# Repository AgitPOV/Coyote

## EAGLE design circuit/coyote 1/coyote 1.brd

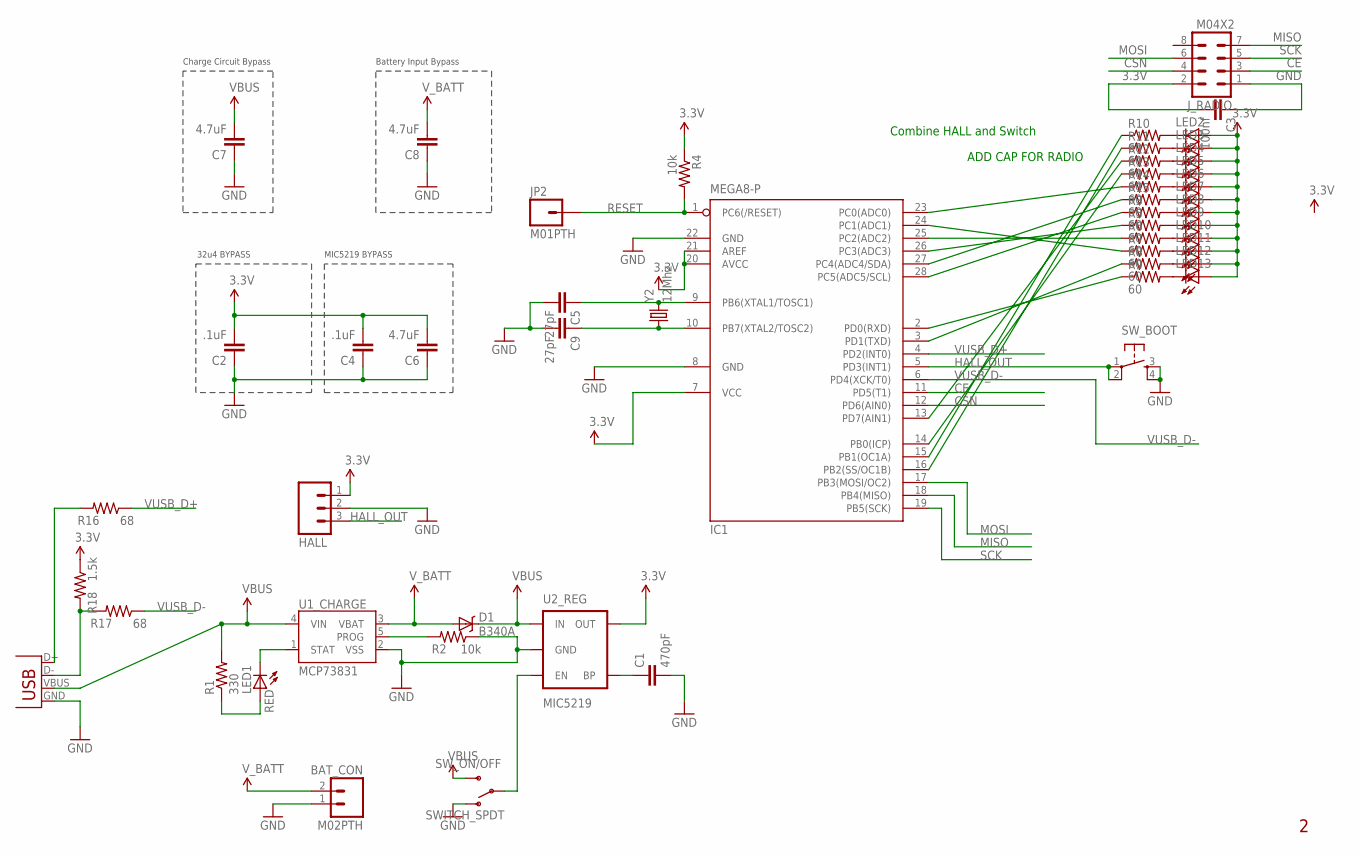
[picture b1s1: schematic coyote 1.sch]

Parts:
BAT_CON: M02PTH; 1X02
C1: 470pF; 1206
C2, C4: .1uF; 1206
C3: 100nf; 1206
C5, C9: 27pF; 1206
C6, C7, C8: 4.7uF; 1206
D1: B340A; SMA-DIODE
HALL: M03PTH; 1X03
IC1: MEGA8-P; DIL28-3
JP1: USB-MB-H
JP2: M01PTH; 1X01
J_RADIO: M04X2; 2X4
LED1: RED; LED-1206
LED2, LED3, LED4, LED5, LED6, LED7, LED8, LED9, LED10, LED11, LED12, LED13: LED1206; LED-1206
R1: 330; 1206
R2, R4: 10k; 1206
R3, R5, R6, R7, R8, R9, R10, R11, R12, R13, R14, R15: 60; 1206
R16, R17: 68; 1206
R18: 1.5k; 1206
SW_BOOT: TAC_SWITCHPTH; TACTILE-PTH
SW_ON/OFF: SWITCH_SPDT; KPS-1290
U1_CHARGE: MCP73831; SOT23-5
U2_REG: MIC5219; SOT23-5
Y2: 12Mhz; HC49US

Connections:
3.3V: C2.2, C3.2, C4.2, C6.2, HALL.1, IC1.7 (VCC), IC1.20 (AVCC), IC1.21 (AREF), J_RADIO.2, LED2.A, LED3.A, LED4.A, LED5.A, LED6.A, LED7.A, LED8.A, LED9.A, LED10.A, LED11.A, LED12.A, LED13.A, R4.1, R18.1, U2_REG.5 (OUT)
5V: C7.2, D1.C, JP1.VBUS, R1.2, SW_ON/OFF.S, U1_CHARGE.4 (VIN), U2_REG.1 (IN)
CE: IC1.11 (PD5(T1)), J_RADIO.3
CSN: IC1.12 (PD6(AIN0)), J_RADIO.4
D+: JP1.D+, R16.2
D-: JP1.D-, R17.2, R18.2
GND: BAT_CON.1, C1.2, C2.1, C3.1, C4.1, C5.2, C6.1, C7.1, C8.1, C9.2, HALL.2, IC1.8 (GND), IC1.22 (GND), JP1.GND, J_RADIO.1, R2.1, SW_BOOT.3, SW_BOOT.4, SW_ON/OFF.O, U1_CHARGE.2 (VSS), U2_REG.2 (GND)
HALL_OUT: HALL.3, IC1.5 (PD3(INT1)), SW_BOOT.1, SW_BOOT.2
MISO: IC1.18 (PB4(MISO)), J_RADIO.7
MOSI: IC1.17 (PB3(MOSI/OC2)), J_RADIO.6
unnamed: SW_ON/OFF.P, U2_REG.3 (EN)
unnamed: LED1.A, R1.1
unnamed: LED1.C, U1_CHARGE.1 (STAT)
unnamed: LED8.C, R3.2
unnamed: R2.2, U1_CHARGE.5 (PROG)
unnamed: LED9.C, R5.2
unnamed: C1.1, U2_REG.4 (BP)
unnamed: LED10.C, R6.2
unnamed: IC1.13 (PD7(AIN1)), R12.1
unnamed: LED11.C, R7.2
unnamed: LED12.C, R8.2
unnamed: LED13.C, R9.2
unnamed: LED2.C, R10.2
unnamed: LED3.C, R11.2
unnamed: LED4.C, R12.2
unnamed: LED5.C, R13.2
unnamed: LED6.C, R14.2
unnamed: LED7.C, R15.2
unnamed: IC1.15 (PB1(OC1A)), R10.1
unnamed: IC1.16 (PB2(SS/OC1B)), R11.1
unnamed: IC1.14 (PB0(ICP)), R13.1
unnamed: IC1.2 (PD0(RXD)), R9.1
unnamed: IC1.3 (PD1(TXD)), R8.1
unnamed: IC1.23 (PC0(ADC0)), R14.1
unnamed: IC1.27 (PC4(ADC4/SDA)), R15.1
unnamed: IC1.28 (PC5(ADC5/SCL)), R3.1
unnamed: IC1.24 (PC1(ADC1)), R7.1
unnamed: IC1.25 (PC2(ADC2)), R6.1
unnamed: IC1.26 (PC3(ADC3)), R5.1
unnamed: C5.1, IC1.9 (PB6(XTAL1/TOSC1)), Y2.2
unnamed: C9.1, IC1.10 (PB7(XTAL2/TOSC2)), Y2.1
RESET: IC1.1 (PC6(/RESET)), JP2.1, R4.2
SCK: IC1.19 (PB5(SCK)), J_RADIO.5
VUSB_D+: IC1.4 (PD2(INT0)), R16.1
VUSB_D-: IC1.6 (PD4(XCK/T0)), R17.1
V_BATT: BAT_CON.2, C8.2, D1.A, U1_CHARGE.3 (VBAT)

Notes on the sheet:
32u4 BYPASS
MIC5219 BYPASS
Charge Circuit Bypass
Battery Input Bypass
ADD CAP FOR RADIO
Combine HALL and Switch

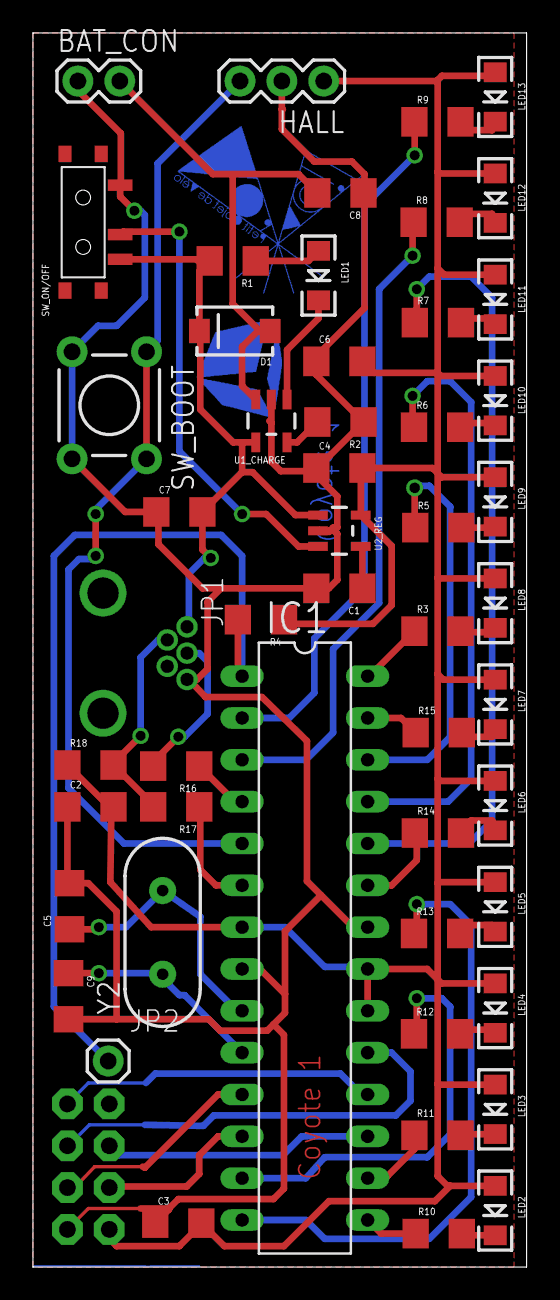
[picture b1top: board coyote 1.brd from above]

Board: 2 copper layers, 30.0 x 74.9 mm, 52 parts (1 on the bottom side), 46 nets.

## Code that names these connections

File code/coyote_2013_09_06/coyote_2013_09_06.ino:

/*
 $$$$$$\   $$$$$$\  $$$$$$\ $$$$$$$$\       $$$$$$$\   $$$$$$\  $$\    $$\         $$$$$$\   $$$$$$\ $$\     $$\  $$$$$$\ $$$$$$$$\ $$$$$$$$\ 
 $$  __$$\ $$  __$$\ \_$$  _|\__$$  __|      $$  __$$\ $$  __$$\ $$ |   $$ |       $$  __$$\ $$  __$$\\$$\   $$  |$$  __$$\\__$$  __|$$  _____|
 $$ /  $$ |$$ /  \__|  $$ |     $$ |         $$ |  $$ |$$ /  $$ |$$ |   $$ |       $$ /  \__|$$ /  $$ |\$$\ $$  / $$ /  $$ |  $$ |   $$ |      
 $$$$$$$$ |$$ |$$$$\   $$ |     $$ |         $$$$$$$  |$$ |  $$ |\$$\  $$  |       $$ |      $$ |  $$ | \$$$$  /  $$ |  $$ |  $$ |   $$$$$\    
 $$  __$$ |$$ |\_$$ |  $$ |     $$ |         $$  ____/ $$ |  $$ | \$$\$$  /        $$ |      $$ |  $$ |  \$$  /   $$ |  $$ |  $$ |   $$  __|   
 $$ |  $$ |$$ |  $$ |  $$ |     $$ |         $$ |      $$ |  $$ |  \$$$  /         $$ |  $$\ $$ |  $$ |   $$ |    $$ |  $$ |  $$ |   $$ |      
 $$ |  $$ |\$$$$$$  |$$$$$$\    $$ |         $$ |$$\    $$$$$$  |$$\\$  /$$\       \$$$$$$  | $$$$$$  |   $$ |     $$$$$$  |  $$ |   $$$$$$$$\ 
 \__|  \__| \______/ \______|   \__|         \__|\__|   \______/ \__|\_/ \__|       \______/  \______/    \__|     \______/   \__|   \________|
 
 */


/*  
 
 POV PIN CONFIGURTATION
 ==========================
 
 LED    ATMEGA168     ARDUINO PIN
 13     PD0           0
 12     PD1           1
 11     PC1           A1
 10     PC2           A2
 9      PC3           A3
 8      PC5           A5
 7      PC4           A4
 6      PC0           A0
 5      PB0           8
 4      PD7           7
 3      PB2           10
 2      PB1           9
 
 ARDUINO 
 ATMEGA168     PIN  INTERRUPT
 HALL   PD3           3    1
 
 */
unsigned char ledPins[]={
  9,10,7,8,A0,A4,A5,A3,A2,A1,1,0};

#define HALL_INTERRUPT 1
#define HALL_PIN 3





void setup() {                

  povSetup();
  povSetMessage("COYOTE");

  // A 3s fade out animation  
  unsigned long timeStamp = millis();
  unsigned long microTimeStamp = micros();
  while ( (millis() - timeStamp) < 3000) {

    unsigned long lapsed = (micros() - microTimeStamp); // 0-3000000 

    unsigned long dim = lapsed / 300; // 0-10000
    unsigned long frame = lapsed % 10000; //0-10000

      if ( frame >= dim ) {
      for ( int i=0; i < 12 ; i++ ) digitalWrite( ledPins[i],  LOW ); //ON
    } 
    else {
      for ( int i=0; i < 12 ; i++ ) digitalWrite( ledPins[i],  HIGH ); //OFF
    }



  }

  // Turn LEDS off
  for (unsigned char k=0;k<12;k++) {
    digitalWrite(ledPins[k],HIGH);
  }
}


void loop() {

  povWaitAndDisplay();

}

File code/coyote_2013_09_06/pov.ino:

/*
 * AgitPOV
 * 12-LED POV for Arduino
 * Can display both latin and arabic letters.
 *
 * (c) 2011-2012
 
 VERSION
 2.1 for COYOTE
 
 CHANGES
 2.1 : 
 changed ledPins to ledPins
 
 2.0 : 
 includes Pinky board and interruption
 
 
 Thomas O Fredericks
 Alan Kwok
 
 *       Alexandre Castonguay
 *       Sofian Audry
 *       Jean-Pascal Bellemare
 * (c) 2013, Changes: 7 leds to 12 and 5 to 7
 *		 Daniel Felipe Valencia
 *		 dfvalen0223@gmail.com
 * (c) 2013, Changes: added new pinout for 12 leds
 *               Andre Girard
 *               andre@andre-girard.com 
 *
 * This program is free software: you can redistribute it and/or modify
 * it under the terms of the GNU General Public License as published by
 * the Free Software Foundation, either version 3 of the License, or
 * (at your option) any later version.
 *
 * This program is distributed in the hope that it will be useful,
 * but WITHOUT ANY WARRANTY; without even the implied warranty of
 * MERCHANTABILITY or FITNESS FOR A PARTICULAR PURPOSE.  See the
 * GNU General Public License for more details.
 *
 * You should have received a copy of the GNU General Public License
 * along with this program.  If not, see <http://www.gnu.org/licenses/>.
 */

#include <avr/pgmspace.h>
#include <string.h>


#ifndef POV_USE_ARABIC
#define POV_USE_LATIN
#endif




/*********************************************** LED MAPPING

Pinky LED : ATMEGA168 : Arduino
LED0-LED5 : PB0-PB5 : 8,9,10,11,12,13
LED6-LED11 : PC0-PC5 : AN0, AN1, AN2, AN3, AN4, AN5

PINKY
unsigned char ledPins[]={8,9,10,11,12,13,A0,A1,A2,A3,A4,A5};
POV
unsigned char ledPins[]={18,19,4,5,6,7,8,9,10,11,12,13};

*/




/*********************************************** INTERRUPT MAPPING

what : interrupt : ATMEGA168 : Arduino
hall : 0 : PD2 : 2
 
PINKY
#define HALL_INTERRUPT 0
#define HALL_PIN 2
 
*/




volatile boolean povDoIt = false;




// Letter width. since i have 12 LED, then each letter would look like a 12 x 7 matrix
#define POV_WIDTH 7
#define POV_MAX_MESSAGE_LENGTH 26
//#define POV_US_BETWEEN_LETTERS 4500
//#define POV_US_BETWEEN_COLUMNS 3300




int16_t povMessage[POV_MAX_MESSAGE_LENGTH];
unsigned char povMessageLength;

unsigned long povIntervalColumns = 3300;
unsigned long povIntervalLetters = 4500;


volatile unsigned long povInterval = 1100;
volatile unsigned long povTimeStamp;



void povSetup() {
  
  // Set up pin 0 - 12 as OUTPUT.
  for (unsigned char k=0;k<12;k++) {
    pinMode(ledPins[k],OUTPUT);
    //digitalWrite(ledPins[k],HIGH);
  }
  
  // initialize HALL with interrupt
  attachInterrupt(HALL_INTERRUPT, hallInterrupt, FALLING);
  pinMode(HALL_PIN, INPUT);
  digitalWrite(HALL_PIN, HIGH);
 
  
}


// LATIN PRIVATE
#ifdef POV_USE_LATIN
prog_uint16_t PROGMEM POV_FONT [][7] =
//uint8_t LATIN_CHARS [][5] =
{
  {
    0x000, 0x000, 0x000, 0x000, 0x000, 0x000, 0x000  }
  , //space
  {
    0x000, 0x000, 0xcff, 0xcff, 0xcff, 0x000, 0x000  }
  , //!
  {
    0x0f0, 0x0f0, 0xfff, 0xfff, 0xfff, 0x0f0, 0x0f0  }
  , //+
  {
    0xf00, 0xf00, 0xf00, 0x000, 0x000, 0x000, 0x000  }
  , //.
  {
    0xc00, 0x600, 0x180, 0x060, 0x018, 0x006, 0x003  }
  , ///
  {
    0x198, 0x198, 0x198, 0x198, 0x198, 0x198, 0x198  }
  , //
  {
    0x01c, 0x007, 0xdc3, 0xdc3, 0x0c3, 0x066, 0x03c  }
  , //?
  {
    0xf80, 0x1f0, 0x19f, 0x183, 0x19f, 0x1f0, 0xf80  }
  , //a
  {
    0xfff, 0xfff, 0xc63, 0xc63, 0xc63, 0xc63, 0x79e  }
  , //b
  {
    0x1f8, 0x7fe, 0x606, 0xc03, 0xc03, 0xf0f, 0x39c  }
  , //c
  {
    0xfff, 0xfff, 0xc03, 0xc03, 0xc03, 0x606, 0x3fc  }
  , //d
  {
    0xfff, 0xfff, 0xe67, 0xe67, 0xe67, 0xe07, 0xe07  }
  , //e
  {
    0xfff, 0xfff, 0x067, 0x067, 0x067, 0x007, 0x007  }
  , //f
  {
    0x1f8, 0x7fe, 0xc03, 0xcc3, 0xcc3, 0xfcf, 0x7cc  }
  , //g
  {
    0xfff, 0xfff, 0x060, 0x060, 0x060, 0xfff, 0xfff  }
  , //h
  {
    0xe07, 0xe07, 0xfff, 0xfff, 0xfff, 0xe07, 0xe07  }
  , //i
  {
    0x3c0, 0xfc0, 0xc07, 0xf07, 0x3ff, 0x0ff, 0x007  }
  , //j
  {
    0xfff, 0xfff, 0x0f0, 0x1f8, 0x79e, 0xe07, 0xc23  }
  , //k
  {
    0xfff, 0xfff, 0xe00, 0xe00, 0xe00, 0xe00, 0xe00  }
  , //l
  {
    0xfff, 0xfff, 0x01e, 0x070, 0x01e, 0xfff, 0xfff  }
  , //m
  {
    0xfff, 0xfff, 0x03c, 0x0e0, 0x380, 0xfff, 0xfff  }
  , //n
  {
    0x3fc, 0x3fc, 0xe07, 0xe07, 0xe07, 0x3fc, 0x3fc  }
  , //o
  {
    0xfff, 0xfff, 0x0c3, 0x0c3, 0x0c3, 0x0c3, 0x07e  }
  , //p
  {
    0x07e, 0x0c3, 0x0e3, 0x3e3, 0x3c3, 0xec3, 0xc7e  }
  , //q
  {
    0xfff, 0xfff, 0x0c3, 0x1c3, 0x3c3, 0x6ff, 0xc7e  }
  , //r
  {
    0x01c, 0xe77, 0xe77, 0xe77, 0xe77, 0xe77, 0x3c0  }
  , //s
  {
    0x007, 0x007, 0xfff, 0xfff, 0xfff, 0x007, 0x007  }
  , //t
  {
    0x3ff, 0x7ff, 0xe00, 0xe00, 0xe00, 0x7ff, 0x3ff  }
  , //u
  {
    0x00f, 0x0f8, 0x7e0, 0xe00, 0x7e0, 0x0f8, 0x01f  }
  , //v
  {
    0x01f, 0x0f0, 0xf80, 0x0ff, 0xf80, 0x0f0, 0x01f  }
  , //w
  {
    0xe07, 0x30c, 0x198, 0x0f0, 0x198, 0x30c, 0xe07  }
  , //x
  {
    0x00f, 0x038, 0x060, 0xfe0, 0x060, 0x038, 0x00f  }
  , //y
  {
    0xe03, 0xf03, 0xf83, 0xcc3, 0xc63, 0xc3f, 0xc0f  } //z

};

void povSetMessage( const char* str) {
  
  povMessageLength = strlen(str);
  povMessageLength = min(povMessageLength, POV_MAX_MESSAGE_LENGTH);
  
  for (int i=0; i<povMessageLength; i++) {
    char c = str[i];
    int16_t a;
    if ('a' <= c && c <= 'z')
      c += 26; // uppercase
    if ('A' <= c && c <= 'Z')
      a = (c - 'A') + 7;
    else {
      switch (c) {
      case ' ': 
        a = 0; 
        break;
      case '!': 
        a = 1; 
        break;
      case '+': 
        a = 2; 
        break;
      case '.': 
        a = 3; 
        break;
      case '/': 
        a = 4; 
        break;
      case '=': 
        a = 5; 
        break;
      case '?': 
        a = 6; 
        break;
      default : 
        a = 0; 
        break;
      }
    }

    povMessage[i] = a;
  }
}



#endif

// povDisplayRaw(LATIN_CHARS, alphaMsg, strlen(msg), 4500, 3300);

//method of displaying the letters. displaying each column (one hex number) of the letter one by one through PORTD. then after a letter, it puts a space in between and move onto the next letter. until however long of the String you wish to display.
//each letter is first turned into ASCII integer, then minus 65. It would then be the row of the letter from the library above. (ex. A is 65 in ASCII, but row 0 in my library)
// furthermore, because of the way i made the hardware, it displays each letter starting from the back of the sentence, and each letter from the right most column.
void povDisplay() { 
  
  
  for (int i = povMessageLength-1; i>=0; i--)
  {
    for (int j = (POV_WIDTH-1); j>=0; j--)
    {
      unsigned int b = pgm_read_word_near(&POV_FONT[povMessage[i]][j]);//message[(int)POVstring[i]-0][j];
//      byte b = fontSet[message[i]][j];
      for (int k=0; k<12; k++) digitalWrite(ledPins[k], bitRead(~b,k));
        delayMicroseconds(povIntervalColumns); //delayMicroseconds(POV_US_BETWEEN_COLUMNS);
    }
    for (int k=0; k<12; k++) digitalWrite(ledPins[k], 1);
      delayMicroseconds(povIntervalLetters); //delayMicroseconds(POV_US_BETWEEN_LETTERS);
      
     
  }
}


void povWaitAndDisplay() {

 // Wait for hall then display
  if ( povDoIt )  {
    
      povIntervalColumns = povInterval  * 30 / 10 ; //povIntervalColumns = interval / 10 * 33 ;
      povIntervalLetters = povInterval  * 43 / 10; //povIntervalLetters = interval / 10 * 45;
   
   
      povIntervalColumns = min(povIntervalColumns,6600);
     povIntervalLetters = min(povIntervalLetters,9000);
     povDisplay();   
     povDoIt = false;
  }
 
 
  
  
}

void hallInterrupt() {
  
  povDoIt = true;
  povInterval = max((millis() - povTimeStamp),2)-1;
  povTimeStamp = millis() ;
  
}

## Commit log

2013-12-24 A little clean-up
2013-12-24 Changed some names
2013-12-24 Updated code version info
2013-12-25 Included PROGMEM
2013-12-25 Removed PROGMEM as it not needed
2013-12-25 Integrated AStream
2014-03-27 Added gerber files and added logos
2014-03-27 Added stencils
2014-04-08 The parts list
    Values and digikey # of parts (+ prices as of 08/04/2014) for the
    Coyote 1 .
2014-04-12 Parts layout
    la carte de l'orientation et des valeurs des pièces par Mariangela.
2014-04-15 Autoformat
2014-04-15 Clipboard.pde -> ClipHelper.pde
2014-04-15 Introduced a new model class for representing pixmaps
2014-04-15 Moved the view and control stuff (except keyPressed()) inside a PixmapEditor class
2014-04-15 Cleanup of debugging comments
2014-04-15 Use mouseDragged() instead of check for mousePressed
2014-04-15 Small cleanup
2014-04-20 Recompiled
2014-04-20 Added constructor to build a pixmap from a pimage
2014-04-20 Added (x,y) positioning of the pixmap editor
2014-04-20 Transferred control of the pen into a tool class
2014-04-20 Implemented basic functionality of a TextTool (now just able to set cursor).
2014-04-20 Stamp function in pixmap (sub-pixmap insert).
2014-04-20 Init pixels to OFF in pixmap
2014-04-20 Bug fix in Pixmap(PImage) constructor: was using bad values
2014-04-20 Une keyTyped() instead of keyPressed() (to allow for unicode characters).
2014-04-20 Cosmetic change
2014-04-20 Reworked with memory string (not tested for RTL).
2014-04-21 Allow backspace.
2014-04-21 Added some predefined constants and moved the editor insode a larger window
2014-04-21 Added a small display for the pen tool (simple dot)
2014-04-21 Refactor and cleanup of editor
2014-04-21 Prevent erase when cursor at beginning
2014-04-21 Use text.isEmpty() instead of checking for "" or length() == 0
2014-04-21 Allow monving the cursor with arrow keys
2014-04-21 Allow insert of key at cursor point
2014-04-21 Cleanup and cosmetic changes
2014-04-21 Bug fix in the computation of the row number according to absolute index.
2014-04-21 Choice of tool (pen / text)
2014-04-21 Added drop-down menu to choose font
2014-04-21 Added simple toggle for LTR/RTL
2014-04-21 Bug fix for RTL (cursor was misplaced)
2014-04-21 Rearrangement of widgets
2014-04-21 Default tool = text
2014-04-21 Export buttons
2014-04-21 Cleanup
2014-04-21 Arapix font
2014-04-21 Cosmetic change in button LTR/RTL
2014-04-21 Increase drastically the length of the editor
2014-04-21 Added erase and invert functions and cleaned up
2014-04-21 Updated and corrected parts layout
2014-04-21 Added a pdf of the parts layout
2014-04-23 Added some more fonts
2014-04-23 Added console
2014-04-23 Added horizontal move tool
2014-04-23 Bugfix for graphics when text has 0 width
2014-04-26 Added comments and a line for continuous display
2014-04-30 Small changes in the fonts
2014-04-30 Added some define hacks for wheel radius adjustments (needs work/refinement)
2014-04-30 Changed the name ACME to POVEditor
2014-05-14 Rename POVEditor -> EditPOV
2014-05-14 Bad renaming: fixed
2014-05-14 Changed colors of the editor to make it sexier
2014-05-14 Added a vertical offset option for fonts
2014-05-15 Cosmetic
2014-05-15 Introduce new factory for text that allows generalization for typing either PFont or image banks with csv file
2014-05-15 Cosmetic (typo) fix
2014-05-15 Added possibility for hexa based fonts + added font from Alex Keeling
2014-05-19 Updating the radio code
2014-05-19 Added xml open and save
2014-05-19 Added a release directory
2014-05-19 Removed the release folder to use the github release instead
2014-05-29 Clean up
    Moved a lot of code to povAcme.ino.
    Added an option for continuous display.
    Added an option to set the column width.
2014-05-29 Updated radio code
2014-05-29 POV should restart if retriggered before it finished
2014-05-29 Added version number
2014-05-29 Updated the fileManager to native Processing code
2014-05-29 Added a wheel display
2014-05-29 Added hardware definitions
2014-06-01 Squashed the wheel display

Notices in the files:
parts and their libraries:
SparkFun-PowerIC: Licensing: CC v3.0 Share-Alike You are welcome to use this library for commercial purposes.
SparkFun-Aesthetics: Released under the Creative Commons
SparkFun-Aesthetics: http://creativecommons.org/licenses/by-sa/3.0
